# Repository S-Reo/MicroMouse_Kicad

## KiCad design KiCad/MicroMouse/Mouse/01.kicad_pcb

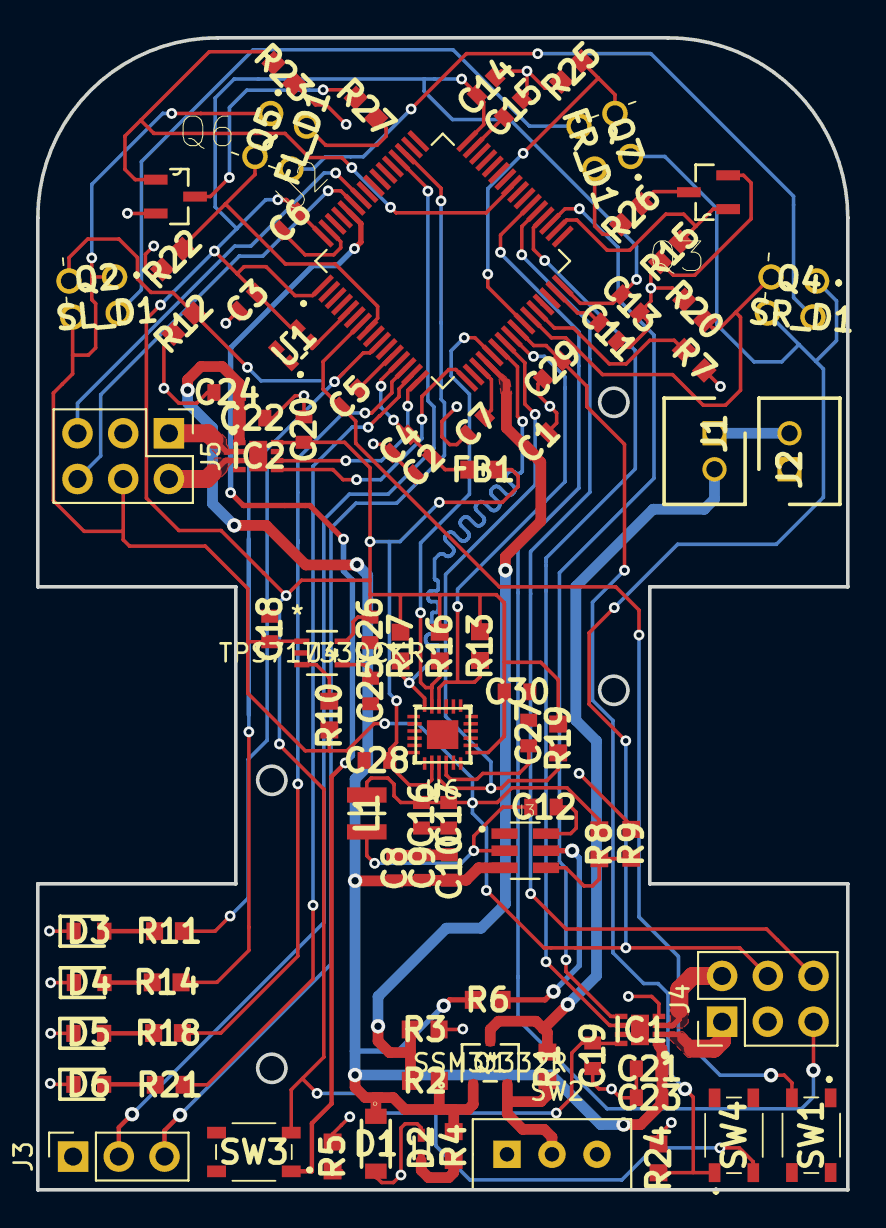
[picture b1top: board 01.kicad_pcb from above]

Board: 2 copper layers, 45.0 x 64.0 mm, 92 parts (0 on the bottom side), 62 nets.

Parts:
C1, C3, C4, C5, C6, C7, C10, C12, C13, C14, C19, C20, C21, C22, C27, C28, C29, C30: 0.1μ; CAPC1608X90N
C2, C18, C26: 1μ; CAPC1608X90N
C8, C9, C23, C24: 10μ; CAPC1608X90N
C11, C15: 2.2μ; CAPC1608X90N
C16, C17: 22μ; CAPC1608X90N
C25: 0.01μ; CAPC1608X90N
D1: KDZVTR9.1B; PMDU
D2: OSO50402C1C; SODFL1608X75N
D3: LED_OSWT1608; LEDC1608X45N
D4: LED_OSTG1608; LEDC1608X45N
D5: LED_OSHR1608; LEDC1608X45N
D6: LED_OSBL1608; LEDC1608X45N
FB1: Ferrite_Bead; BEADC1608X100N
FL_D1: LTE-209; LTE209
FR_D1: LTE-209; LTE209
IC1, IC2: DRV8838DSGT; SON50P200X200X80-9N
J1, J2: PHR-2; SHDR2W50P0X200_1X2_590X450X600P
J3: Conn_01x03_Male; PinSocket_1x03_P2.54mm_Vertical
J4, J5: Conn_02x03_Odd_Even; PinHeader_2x03_P2.54mm_Vertical
L1: 10μ; DFE2HCAH1R0MJ0L
Q1: SSM3J332R; SSM3J332R_LFT
Q2: LTR-4206-SL; LTR4206E
Q3, Q6: IRFML8244
Q4: LTR-4206-SR; LTR4206E
Q5: LTR-4206-FL; LTR4206E
Q7: LTR-4206-FR; LTR4206E
R1, R3, R5, R6, R7, R10, R15, R23, R24: 10k; RESC1608X55N
R2: 20k; RESC1608X55N
R4: 1k; RESC1608X55N
R8: 54.9k_1%; RESC1608X55N
R9: 10k_1%; RESC1608X55N
R11, R14, R18, R21: 330; RESC1608X55N
R12, R20, R22, R25: 698; RESC1608X55N
R13, R16, R17, R19: 4.7k; RESC1608X55N
R26, R27: 130; RESC1608X55N
SL_D1: LTE-209; LTE209
SR_D1: LTE-209; LTE209
SW1, SW3, SW4: SW_MEC_5G; SKRPABE010
SW2: SS12D01G4; SW_SS12D01G4
U1: TG2016SMN; TG2016SMN260000MMCGNNM
U2: STM32F405RGT6; QFP50P1200X1200X160-64N
U3: TPS562200DDCR; SOT95P280X110-6N
U4: TPS71733DCKR
U6: ICM-20648; ICM20648

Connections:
+3V3: C3.1, C6.1, C13.1, C14.1, C19.1, C20.1, C26.1, C28.1, C30.1, FB1.1, IC1.8, IC2.8, R13.2, R16.2, R17.2, R19.2, SW3.3, SW3.4, SW4.3, SW4.4, U1.4, U2.1, U2.32, U2.48, U2.64, U4.5, U6.8, U6.13
AOUT1_MT: IC1.2, J4.1
AOUT2_MT: IC1.3, J4.2
BAT-VOL: C1.1, R2.2, R3.1, U2.20
BOUT1_MT: IC2.2, J5.1
BOUT2_MT: IC2.3, J5.2
BUTTON: C29.1, R24.2, SW4.1, SW4.2, U2.25
EN: C8.1, C9.1, C10.1, C21.1, C22.1, C23.1, C24.1, D1.1, IC1.1, IC2.1, Q1.1, R2.1, R4.1, R6.2, U3.3
ENC-L-A: J5.6, U2.59
ENC-L-B: J5.5, U2.58
ENC-R-A: J4.6, U2.37
ENC-R-B: J4.5, U2.38
EN_Reg: C16.1, C17.1, C18.1, J4.4, J5.4, L1.2, Q2.1, Q4.1, Q5.1, Q7.1, R8.1, R10.2, SL_D1.2, SR_D1.2, U4.1
GND: C1.2, C2.2, C3.2, C4.2, C5.2, C6.2, C7.2, C8.2, C9.2, C10.2, C11.1, C13.2, C14.2, C15.1, C16.2, C17.2, C18.2, C19.2, C20.2, C21.2, C22.2, C23.2, C24.2, C25.2, C26.2, C27.2, C28.2, C29.2, C30.2, D1.2, D2.1, D3.1, D4.1, D5.1, D6.1, IC1.4, IC2.4, J2.1, J3.1, J4.3, J5.3, Q3.2, Q6.2, R3.2, R5.1, R7.2, R9.2, R12.1, R15.2, R20.1, R22.1, R23.2, R24.1, R25.1, SW1.1, SW1.2, SW2.3, U1.2, U2.12, U2.18, U2.63, U3.1, U4.2, U6.11, U6.18, U6.20
LED_1: R21.2, U2.15
LED_2: R18.2, U2.14
LED_3: R14.2, U2.10
LED_4: R11.2, U2.11
MT-A-ENBL: IC1.5, U2.35
MT-A-IN: IC1.6, U2.36
MT-B-ENBL: IC2.5, U2.17
MT-B-IN: IC2.6, U2.16
NCS: R13.1, U2.24, U6.22
unnamed: C2.1, C4.1, FB1.2, U2.13
unnamed: C5.1, SW1.3, SW1.4, U2.7
unnamed: C7.1, U2.19
unnamed: C11.2, U2.31
unnamed: C12.1, R8.2, R9.1, U3.4, U3.6
unnamed: C12.2, L1.1, U3.2
unnamed: C15.2, U2.47
unnamed: C25.1, U4.4
unnamed: C27.1, U6.10
unnamed: D2.2, R4.2
unnamed: D3.2, R11.1
unnamed: D4.2, R14.1
unnamed: D5.2, R18.1
unnamed: D6.2, R21.1
unnamed: FL_D1.1, R27.2
unnamed: FL_D1.2, SR_D1.1
unnamed: FR_D1.1, R26.2
unnamed: FR_D1.2, SL_D1.1
unnamed: J1.1, J2.2
unnamed: J1.2, Q1.3, R1.1
unnamed: Q1.2, R1.2, SW2.2
unnamed: Q3.3, R26.1
unnamed: Q6.3, R27.1
unnamed: R6.1, U3.5
unnamed: R7.1, U2.28
unnamed: R10.1, U4.3
unnamed: U1.3, U2.5
PR-LED-SL-FR: Q3.1, R15.1, U2.34
PR-LED-SR-FL: Q6.1, R23.1, U2.41
PR-RCV-FL: Q5.2, R22.2, U2.8
PR-RCV-FR: Q7.2, R25.2, U2.26
PR-RCV-SL: Q2.2, R12.2, U2.9
PR-RCV-SR: Q4.2, R20.2, U2.27
SCLK: R16.1, U2.21, U6.23
SDIO_N: R19.1, U2.23, U6.9
SDIO_P: R17.1, U2.22, U6.24
USART-RX: J3.2, U2.52
USART-TX: J3.3, U2.51
USR3_BOOT: R5.2, SW3.1, SW3.2, U2.60

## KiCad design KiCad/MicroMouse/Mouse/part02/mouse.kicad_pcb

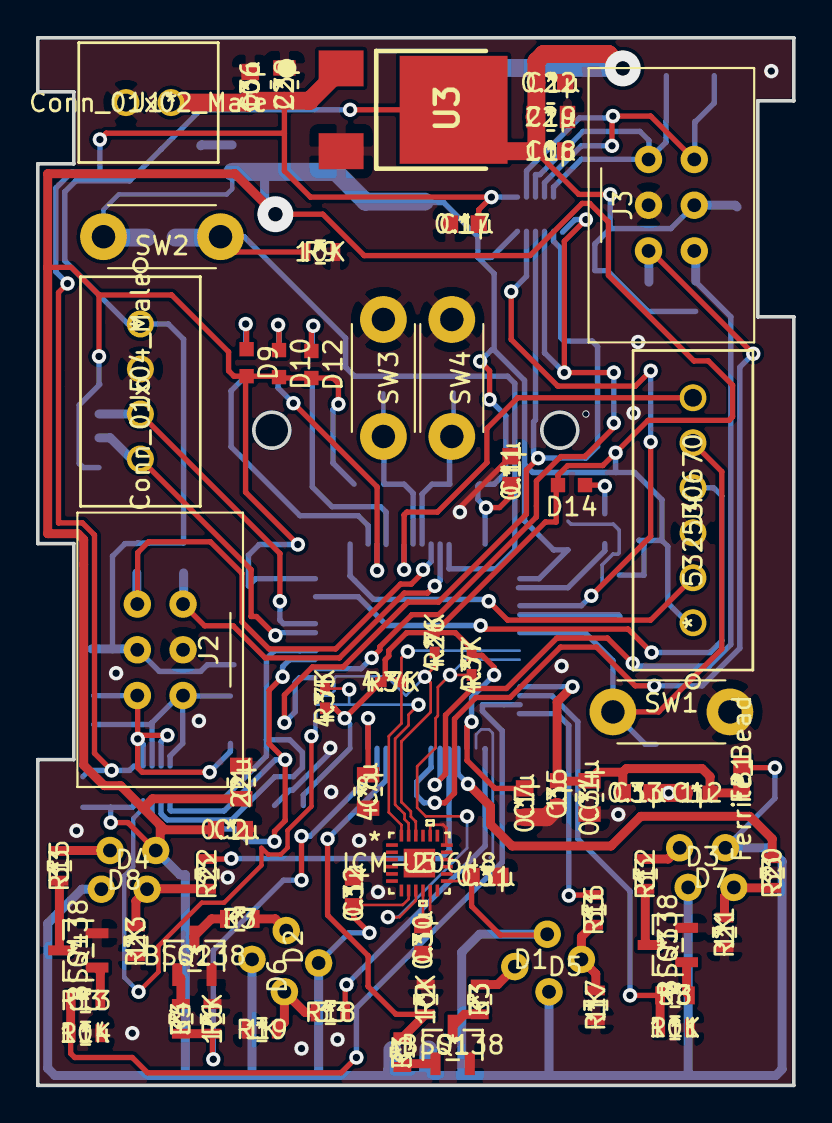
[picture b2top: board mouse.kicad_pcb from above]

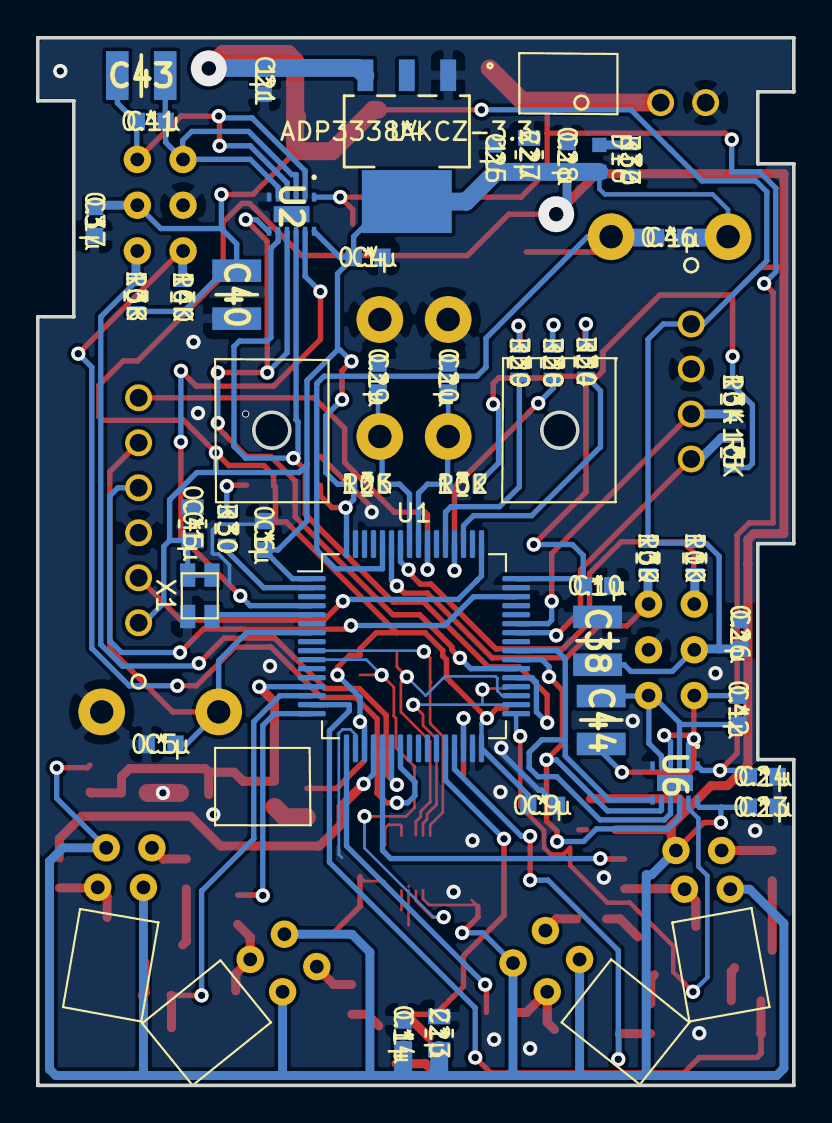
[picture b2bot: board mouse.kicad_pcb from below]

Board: 2 copper layers, 42.0 x 58.2 mm, 115 parts (44 on the bottom side), 68 nets.

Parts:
C1, C13, C19, C27, C39: 22μ; GRM21BR61E106KA73L
C2, C4, C5, C6, C7, C9, C10, C11, C14, C17, C20, C22, C23, C24, C26, C28, C29, C30, C31, C32, C33, C37, C41, C42, C46: 0.1μ; GRM188R6YA106MA73D
C8: 4.7μ; CL21A475KBQNNNE
C12, C21, C25, C35: 1μ; GRM188R71E105KA12D
C18, C36: 10μ; GRM188R6YA106MA73D
C34, C45: 0.01μ; GRM2195C1H103JA01D
C38, C40, C43, C44: 47μ; CAPC3225X270N
D1, D2: LED_OSI5FU3A11C; LBR-127HLD-45
D3, D4: LED_OSI5FU3A11C; LBR-127HLD
D5, D6: L-31ROPT1C; LBR-127HLD-45
D7, D8: L-31ROPT1C; LBR-127HLD
D9: LED_OSHR1608; OSHR1608
D10, D16: LED_OSWT1608; OSHR1608
D12: LED_OSTG1608C1A; OSHR1608
D14: LED_OSBL1608; OSHR1608
FB1: Ferrite_Bead; BLM18PG331SN1D
J1: Conn_01x02_Male; B02B-XASK-1LFSN
J2, J3: Conn_01x06_Male; SEK18_6_2.54mm_2
J4: 532530670; B06B-XASK-1 LFSN
J5: Conn_01x04_Male; B04B-XASK-1LFSN
Q1, Q2, Q3, Q4: BSS138
R1, R3, R4, R7, R8, R12, R13, R15, R16, R18, R20, R22: 33; RR0816Q-330-D
R2, R5, R6, R9, R10, R11, R14, R25, R32, R34, R38, R39, R40: 10K; RG1608N-103-B-T5
R17, R19, R21, R23: 1K; RG1608N-102-B-T5
R24, R28, R29, R30, R33: 330; RG1608P-331-B-T5
R26, R35, R36, R37: 4.7K; MCR01MZPF4701
SW1, SW2, SW3, SW4: SW_Push; TVBP06
U1: STM32F446RETx; LQFP-64_10x10mm_P0.5mm
U2, U6: DRV8835; DRV8835DSSR
U3: NJM2391DL 1-05; NJM2391DL1-05
U4: ADP3338AKCZ-3.3; ADP3338AKCZ-3.3RL7
U5: ICM-20648
X1: 625L3I008M00000; 625L31008M00000

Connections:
+3V3: C1.1, C2.1, C4.1, C6.2, C7.2, C9.2, C10.2, C11.2, C13.1, C14.1, C23.1, C25.1, C27.1, C28.1, C31.1, C32.2, C45.1, C46.1, D1.2, D2.2, D3.2, D4.2, D5.2, D6.2, D7.2, D8.2, D9.2, D10.2, D12.2, D14.2, D16.2, FB1.1, J4.1, R5.1, R25.1, R26.1, R32.1, R34.1, R35.1, R36.1, R37.1, SW2.1, U1.1, U1.19, U1.32, U1.48, U1.64, U2.12, U4.4, U5.8, U5.13, U6.12, X1.1, X1.4
+5V: C18.1, C19.1, C21.1, C22.1, C26.1, C37.1, C38.1, C40.1, J2.4, J3.4, J5.1, R10.1, R38.1, R39.1, R40.1, U3.3, U4.3
+BATT: C17.1, C24.1, C36.1, C39.1, J1.1, U2.1, U3.1, U6.1
AIN1: U1.39, U6.8, U6.10
AIN2: U1.40, U6.7, U6.9
BIN1: U1.37, U2.8, U2.10
BIN2: U1.38, U2.7, U2.9
BOOT0: C46.2, R9.1, SW2.2, U1.60
GND: C1.2, C2.2, C4.2, C5.2, C6.1, C7.1, C8.2, C9.1, C10.1, C11.1, C12.1, C13.2, C14.2, C17.2, C18.2, C19.2, C20.2, C21.2, C22.2, C23.2, C24.2, C25.2, C26.2, C27.2, C28.2, C29.2, C30.2, C31.2, C32.1, C33.1, C34.1, C35.1, C36.2, C37.2, C38.2, C39.2, C40.2, C45.2, J1.2, J2.3, J3.3, J4.3, J5.2, Q1.2, Q2.2, Q3.2, Q4.2, R2.2, R6.2, R9.2, R11.2, R14.2, R17.2, R19.2, R21.2, R23.2, R33.2, SW1.1, SW3.2, SW4.2, U1.12, U1.18, U1.31, U1.47, U1.63, U2.6, U3.2, U4.1, U5.11, U5.18, U5.20, U6.6, X1.2
IMU_CS: R26.2, U1.35, U5.22
IMU_MISO: R37.2, U1.10, U5.9
IMU_MOSI: R36.2, U1.9, U5.24
IMU_SCLK: R35.2, U1.34, U5.23
LED1: R24.2, U1.51
LED1_sensor: R1.2, R2.1, U1.28
LED2: R28.2, U1.52
LED2_sensor: R4.2, R6.1, U1.29
LED3: R29.2, U1.53
LED3_sensor: R8.2, R11.1, U1.14
LED4: R30.2, U1.2
LED4_sensor: R13.2, R14.1, U1.15
unnamed: C5.1, J4.5, SW1.2, U1.7
unnamed: C8.1, U1.30
unnamed: C12.2, C33.2, C34.2, C35.2, FB1.2, U1.13
unnamed: C30.1, U5.10
unnamed: C41.1, C43.1, J3.2, U2.2, U2.4
unnamed: C41.2, C43.2, J3.1, U2.3, U2.5
unnamed: C42.1, C44.1, J2.2, U6.2, U6.4
unnamed: C42.2, C44.2, J2.1, U6.3, U6.5
unnamed: D1.1, R3.1
unnamed: D2.1, R7.1
unnamed: D3.1, R12.1
unnamed: D4.1, R15.1
unnamed: D5.1, R16.1, R17.1
unnamed: D6.1, R18.1, R19.1
unnamed: D7.1, R20.1, R21.1
unnamed: D8.1, R22.1, R23.1
unnamed: D9.1, R24.1
unnamed: D10.1, R28.1
unnamed: D12.1, R29.1
unnamed: D14.1, R30.1
unnamed: D16.1, R33.1
unnamed: J4.2, U1.49
unnamed: J4.4, U1.46
unnamed: J4.6, U1.55
unnamed: J5.3, R34.2, U1.43
unnamed: J5.4, R5.2, U1.42
unnamed: Q1.1, R1.1
unnamed: Q1.3, R3.2
unnamed: Q2.1, R4.1
unnamed: Q2.3, R7.2
unnamed: Q3.1, R8.1
unnamed: Q3.3, R12.2
unnamed: Q4.1, R13.1
unnamed: Q4.3, R15.2
unnamed: U1.5, X1.3
Photo1_sensor: R16.2, U1.16
Photo2_sensor: R18.2, U1.17
Photo3_sensor: R20.2, U1.20
Photo4_sensor: R22.2, U1.21
STBY_HorL_A: U1.33, U6.11
STBY_HorL_B: U1.4, U2.11
SW1: C20.1, R32.2, SW3.1, U1.56
SW2: C29.1, R25.2, SW4.1, U1.57
TIM_CH1A: J2.6, R10.2, U1.58
TIM_CH1B: J2.5, R39.2, U1.59
TIM_CH2A: J3.6, R38.2, U1.22
TIM_CH2B: J3.5, R40.2, U1.23

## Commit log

2021-07-07 kicadデータ全部乗せ!

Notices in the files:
parts and their libraries:
Copyright 2016 Accelerated Designs. All rights reserved.
